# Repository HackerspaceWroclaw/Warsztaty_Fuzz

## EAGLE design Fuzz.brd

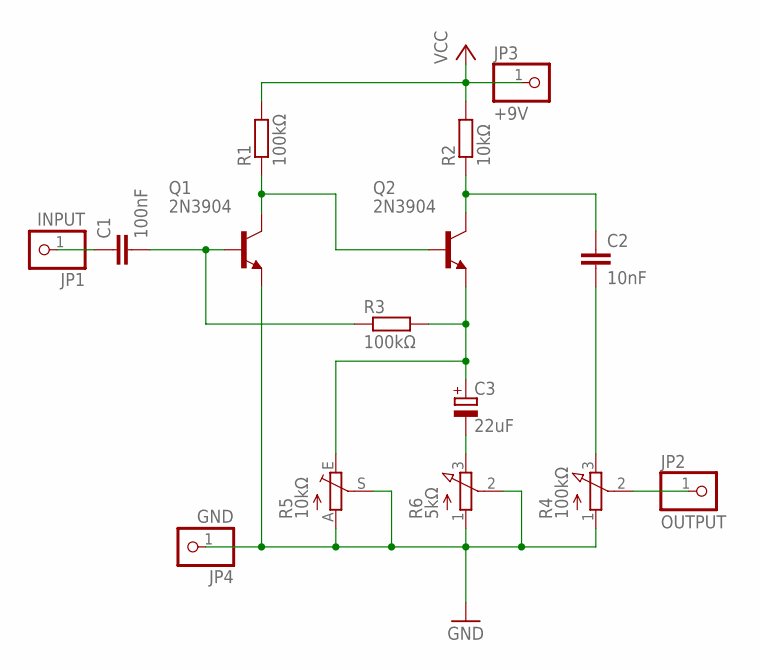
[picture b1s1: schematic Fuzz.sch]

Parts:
C1: 100nF; C050-024X044
C2: 10nF; C050-024X044
C3: 22uF; E5-5
JP1: INPUT; 1X01
JP2: OUTPUT; 1X01
JP3: +9V; 1X01
JP4: GND; 1X01
Q1, Q2: 2N3904; TO92-EBC
R1, R3: 100kΩ; 0207/10
R2: 10kΩ; 0207/10
R4: 100kΩ; 3RP/1610N
R5: 10kΩ; CA6V
R6: 5kΩ; 3RP/1610N

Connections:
GND: JP4.1, Q1.E, R4.1 (A), R5.A, R5.S, R6.1 (A), R6.2 (S)
INPUT: C1.1, JP1.1
unnamed: C1.2, Q1.B, R3.1
unnamed: Q1.C, Q2.B, R1.1
unnamed: C2.1, Q2.C, R2.1
unnamed: C2.2, R4.3 (E)
unnamed: C3.+, Q2.E, R3.2, R5.E
unnamed: C3.-, R6.3 (E)
OUTPUT: JP2.1, R4.2 (S)
VCC: JP3.1, R1.2, R2.2

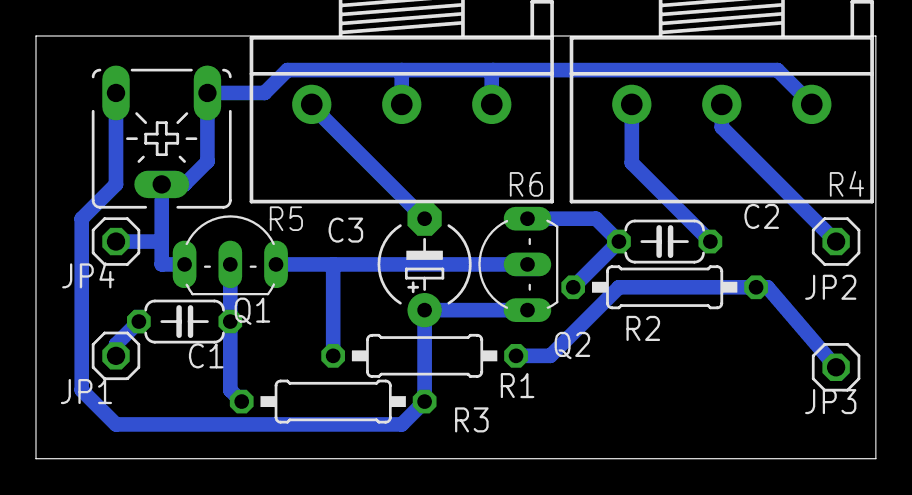
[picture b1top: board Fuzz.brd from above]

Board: 2 copper layers, 46.7 x 23.5 mm, 15 parts (0 on the bottom side), 10 nets.

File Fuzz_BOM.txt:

Partlist

Exported from FuzzFace.sch at 2018-08-13 23:11:18

EAGLE Version 6.4.0 Copyright (c) 1988-2013 CadSoft

Assembly variant: 

Part     Value          Device          Package      Library    Sheet

C1       10nF           C-EU050-024X044 C050-024X044 rcl        1
C2       10nF           C-EU050-024X044 C050-024X044 rcl        1
C3       22uF           CPOL-EUE5-5     E5-5         rcl        1
JP1      INPUT          PINHD-1X1       1X01         pinhead    1
JP2      OUTPUT         PINHD-1X1       1X01         pinhead    1
JP3      +9V            PINHD-1X1       1X01         pinhead    1
JP4      GND            PINHD-1X1       1X01         pinhead    1
Q1       2N3904         -NPN-TO92-EBC   TO92-EBC     transistor 1
Q2       2N3904         -NPN-TO92-EBC   TO92-EBC     transistor 1
R1       100k           R-EU_0207/10    0207/10      rcl        1
R2       10k            R-EU_0207/10    0207/10      rcl        1
R3       100k           R-EU_0207/10    0207/10      rcl        1
R4       100k           3RP/1610N       3RP/1610N    pot        1
R5       10k            TRIM_EU-CA6V    CA6V         pot        1
R6       5k             3RP/1610N       3RP/1610N    pot        1

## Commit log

2019-07-26 Fuzz: pierwsza wersja materiałów
